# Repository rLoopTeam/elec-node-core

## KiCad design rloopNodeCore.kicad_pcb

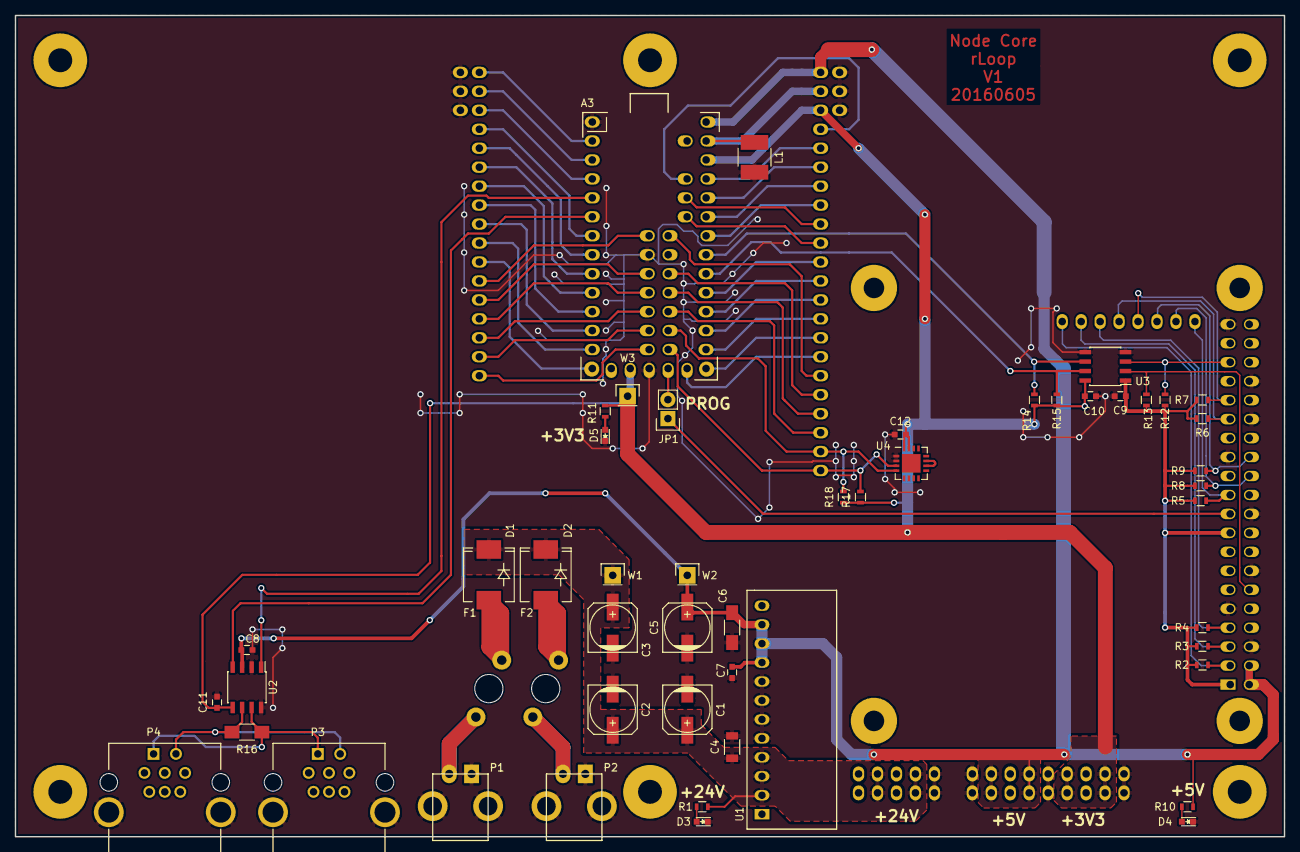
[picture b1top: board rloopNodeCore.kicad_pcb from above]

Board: 2 copper layers, 170.0 x 110.0 mm, 53 parts (1 on the bottom side), 68 nets.

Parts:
A1: NODE_CORE_CONNECTOR; NODECORE
A2: RASPI_2B; Raspberry-Pi-2-Model-B
A3: Teensy_3.2; TEENSY-3.2
C1, C2, C3, C5: 100uF; c_elec_6.3x5.8
C4: 1uF; C_1206
C6: 10uF; C_1206_HandSoldering
C7: 1uF; C_0603
C8, C9, C10, C11, C12: 100nF; C_0603
D1, D2: D; SMC_Standard
D3, D4, D5: LED; LED_0603
F1, F2: FUSE; FUSEHOLDER-BLADE-LITTELFUSE-153
JP1: Jumper_NO_Small; Pin_Header_Straight_1x02
L1: FERRITE_INDUCTOR; NR4018_HandSoldering
P1, P2: PWR_CONN_1X2; CONN-TE-MICROMNL-2-PTH-MALE-RGT
P3: CAN_IN_M12; M12-TE-5-2172077-2
P4: CAN_OUT_M12; M12-TE-5-2172077-2
R1, R10, R11: 1K2; R_0603
R2, R3, R4, R5, R6, R7, R8, R9: 10K; R_0603
R12, R13: 1k; R_0603
R14, R15: 1K; R_0603
R16: 120; R_1206_HandSoldering
R17, R18: 2K2; R_0603
U1: R-625.0P; R-6xxxP
U2: MCP2562; SOIC-8_3.9x4.9mm_Pitch1.27mm
U3: ISO1540; SOIC-8_3.9x4.9mm_Pitch1.27mm
U4: TYS01; QFN-16-1EP_4x4mm_Pitch0.65mm
W1, W2, W3: TEST_1P; Pin_Header_Straight_1x01

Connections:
3V3_PI: A2.1, A2.17, C9.1, R2.2, R3.2, R4.2, R5.2, R6.2, R7.2, R8.2, R9.2, R12.1, R13.1, U3.1
+3V3: A1.+3V3, A3.+3V3, C10.1, C11.1, C12.1, R11.1, R14.1, R15.1, R17.1, R18.1, U2.5, U3.8, U4.15, U4.16, W3.1
+5V: A1.+5V, A2.2, A2.4, A3.VIN, C5.1, C6.1, C7.1, C8.1, R10.1, U1.9, U1.10, U1.11, U2.3, W2.1
+24V: A1.+24V, C1.1, C2.1, C3.1, C4.1, D1.1, D2.1, R1.1, U1.2, U1.3, U1.4, W1.1
A10: A1.A10, A3.A10
A11: A1.A11, A3.A11
A12: A1.A12, A3.A12
A13: A1.A13, A3.A13
A14: A1.A14, A3.A14
AREF: A1.AREF, A3.AREF
GND: A1.GND, A2.6, A2.9, A2.14, A2.20, A2.25, A2.30, A2.34, A2.39, A3.GND1, A3.GND2, A3.GND3, C1.2, C2.2, C3.2, C4.2, C5.2, C6.2, C7.2, C8.2, C9.2, C10.2, C11.2, C12.2, D3.1, D4.1, D5.1, L1.1, P1.1, P1.M1, P1.M2, P2.1, P2.M1, P2.M2, P3.M1, P3.M2, P4.M1, P4.M2, U1.5, U1.6, U1.7, U1.8, U2.2, U2.8, U3.4, U3.5, U4.1, U4.2
GNDA: A1.AGND, A3.AGND, L1.2
ID1: A1.ID1, A2.3, R2.1
ID2: A1.ID2, A2.5, R3.1
ID3: A1.ID3, A2.7, R4.1
ID4: A1.ID4, A2.29, R6.1
ID5: A1.ID5, A2.31, R7.1
ID6: A1.ID6, A2.26, R9.1
ID7: A1.ID7, A2.24, R8.1
ID8: A1.ID8, A2.21, R5.1
unnamed: A3.18, R15.2, U3.7
unnamed: A3.19, R14.2, U3.6
unnamed: A3.PROG, JP1.2
unnamed: D1.2, F1.2
unnamed: D2.2, F2.2
unnamed: D3.2, R1.2
unnamed: D4.2, R10.2
unnamed: D5.2, R11.2
unnamed: F1.1, P1.2
unnamed: F2.1, P2.2
unnamed: P3.1, P4.1, R16.1, U2.7
unnamed: P3.2, P4.2, R16.2, U2.6
unnamed: U4.10, U4.11
PI_SCL: A2.35, R12.2, U3.3
PI_SDA: A2.12, R13.2, U3.2
PROG: A2.19, JP1.1
SCL: A1.T29, A3.29, R17.2, U4.3
SDA: A1.T30, A3.30, R18.2, U4.4
T0: A1.T0, A3.0
T1: A1.T1, A3.1
T2: A1.T2, A3.2
T5: A1.T5, A3.5
T6: A1.T6, A3.6
T7: A1.T7, A3.7
T8: A1.T8, A3.8
T9: A1.T9, A3.9
T10: A1.T10, A3.10
T11: A1.T11, A3.11
T12: A1.T12, A3.12
T13: A1.T13, A3.13
T14: A1.T14, A3.14
T15: A1.T15, A3.15
T16: A1.T16, A3.16
T17: A1.T17, A3.17
T20: A1.T20, A3.20
T21: A1.T21, A3.21
T22: A1.T22, A3.22
T23: A1.T23, A3.23
T24: A1.T24, A3.24
T25: A1.T25, A3.25
T26: A1.T26, A3.26
T27: A1.T27, A3.27
T28: A1.T28, A3.28
T31: A1.T31, A3.31
T32: A1.T32, A3.32
T33: A1.T33, A3.33
TEENSY_CAN_RX: A3.4, U2.4
TEENSY_CAN_TX: A3.3, U2.1

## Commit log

2016-04-01 :circus_tent: Added .gitattributes & .gitignore files
2016-04-28 First draft!
2016-05-05 v0.2
    Added I2C isolator
    Added 24V input diode
    Added power rail test points and indicator LEDs
    More power supply filter caps
2016-05-08 v0.3
    Added optional ferrite choke between GND and AGND
    Isolated I2C transceiver supply voltages
    Removed CAN from Node Core Connector
    Added program pin jumper
2016-05-09 Formatting Improvements
2016-05-11 5/09
2016-05-16 just seeing how big everything is
2016-06-06 node core is almost done, awaiting review
2016-06-12 minor routing changes, some more vias
2016-06-13 F2 was offset by a single hair
2016-06-13 recovered lost ground traces
2016-06-18 Print Schematic for Review Team.
